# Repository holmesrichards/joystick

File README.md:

# Analog Output Joystick

This is a Kosmo format synth module that provides an interface for an analog joystick. The X and Y outputs provide control voltages that vary with the horizontal and vertical positions, respectively, of the joystick.

There are range control pots for X and Y. These adjust the width of the control voltage range. With the width fully clockwise the control voltage range is about 10 V end to end.

There also are offset control pots. These add a DC offset of between -5 V and 5 V to the output. So with the range pot at maximum and the offset pot centered the output voltage ranges from about -5 V to 5 V; with the offset pot fully clockwise the output voltage range is about 0 V to 10 V.

The X output voltage increases as you move the joystick from left to right, and Y increases from down to up. There also are two inverted output jacks; here the X output increases from right to left and the Y increases from up to down. Both outputs have the same range and same offset (with same sign), so for instance if the regular output is from 0 V to 10 V left to right, the inverted output will be 10 V to 0 V left to right.

## Current draw
16 mA +12 V, 16 mA -12 V

## Photos

## Documentation

* [Schematic](Docs/joystick.pdf)
* PCB layout: [front](Docs/joystick_layout_front.pdf), [back](Docs/joystick_layout_back.pdf)
* [BOM](Docs/joystick_bom.md)
* [Build notes](Docs/build.md)
* [How it works](Docs/howitworks.md)

## GitHub repository

* [https://github.com/holmesrichards/joystick](https://github.com/holmesrichards/joystick)

## Submodules

This repo uses submodules aoKicad and Kosmo_panel, which provide needed libaries for KiCad. To clone:

```
git clone git@github.com:holmesrichards/joystick.git
git submodule init
git submodule update
```

Alternatively do

```
git clone --recurse-submodules git@github.com:holmesrichards/joystick.git
```

Or if you download the repository as a zip file, you must also click on the "aoKicad" and "Kosmo\_panel" links on the GitHub page (they'll have "@ something" after them) and download them as separate zip files which you can unzip into this repo's aoKicad and Kosmo\_panel directories.

If desired, copy the files from aoKicad and Kosmo\_panel to wherever you prefer (your KiCad user library directory, for instance, if you have one). Then in KiCad, add symbol libraries 

```
aoKicad/ao_symbols
Kosmo_panel/Kosmo
```
and footprint libraries 
```
aoKicad/ao_tht
Kosmo_panel/Kosmo_panel.
```

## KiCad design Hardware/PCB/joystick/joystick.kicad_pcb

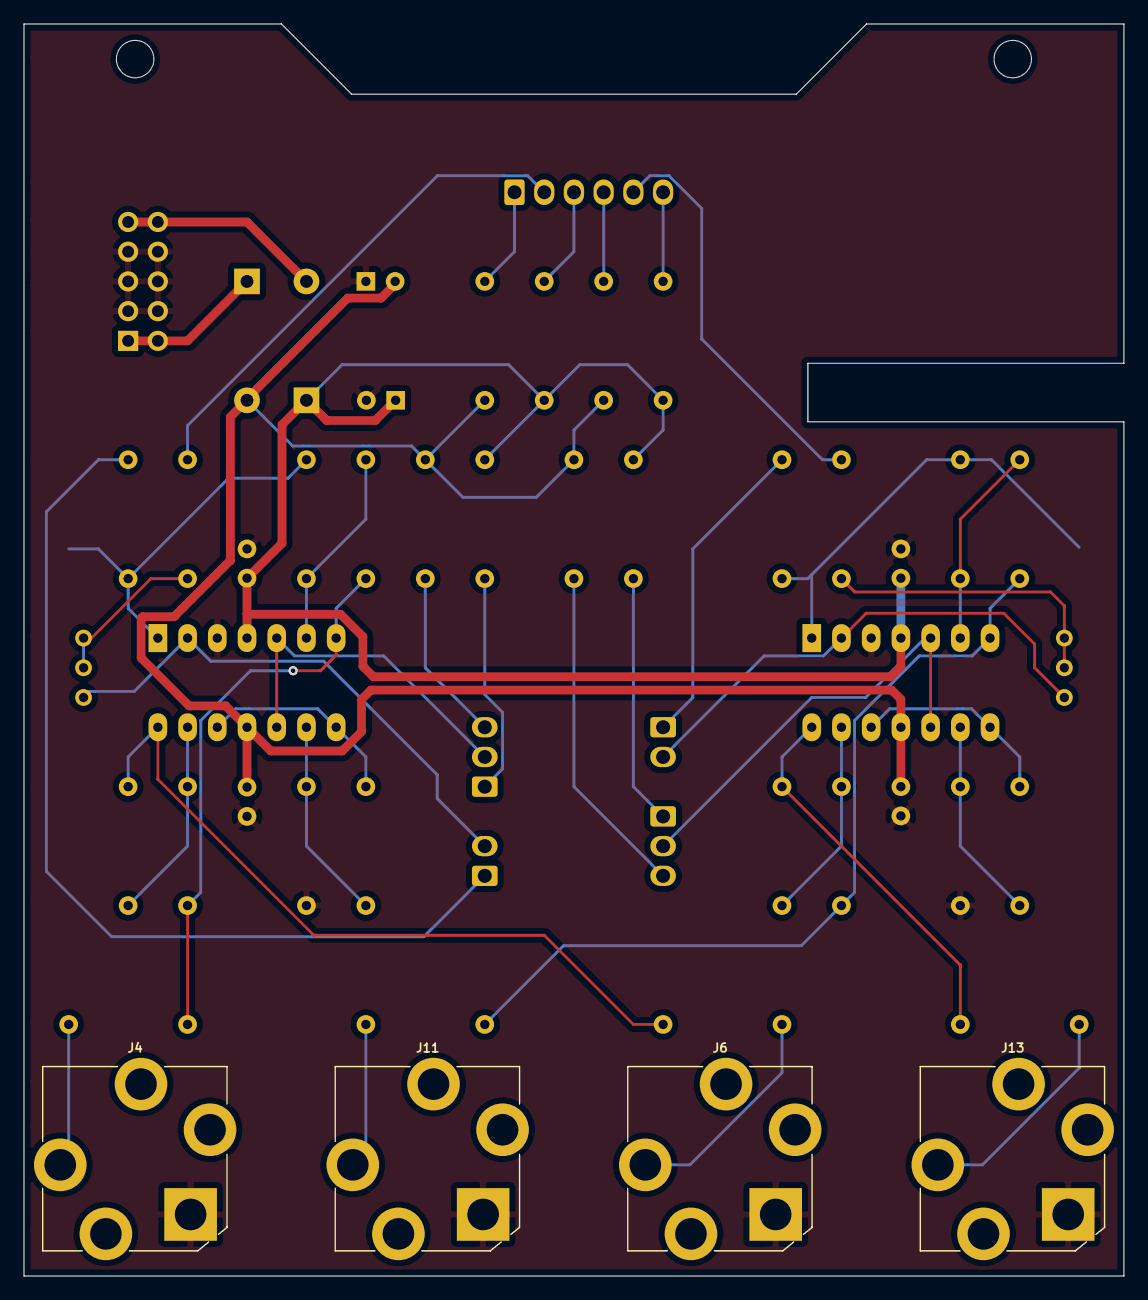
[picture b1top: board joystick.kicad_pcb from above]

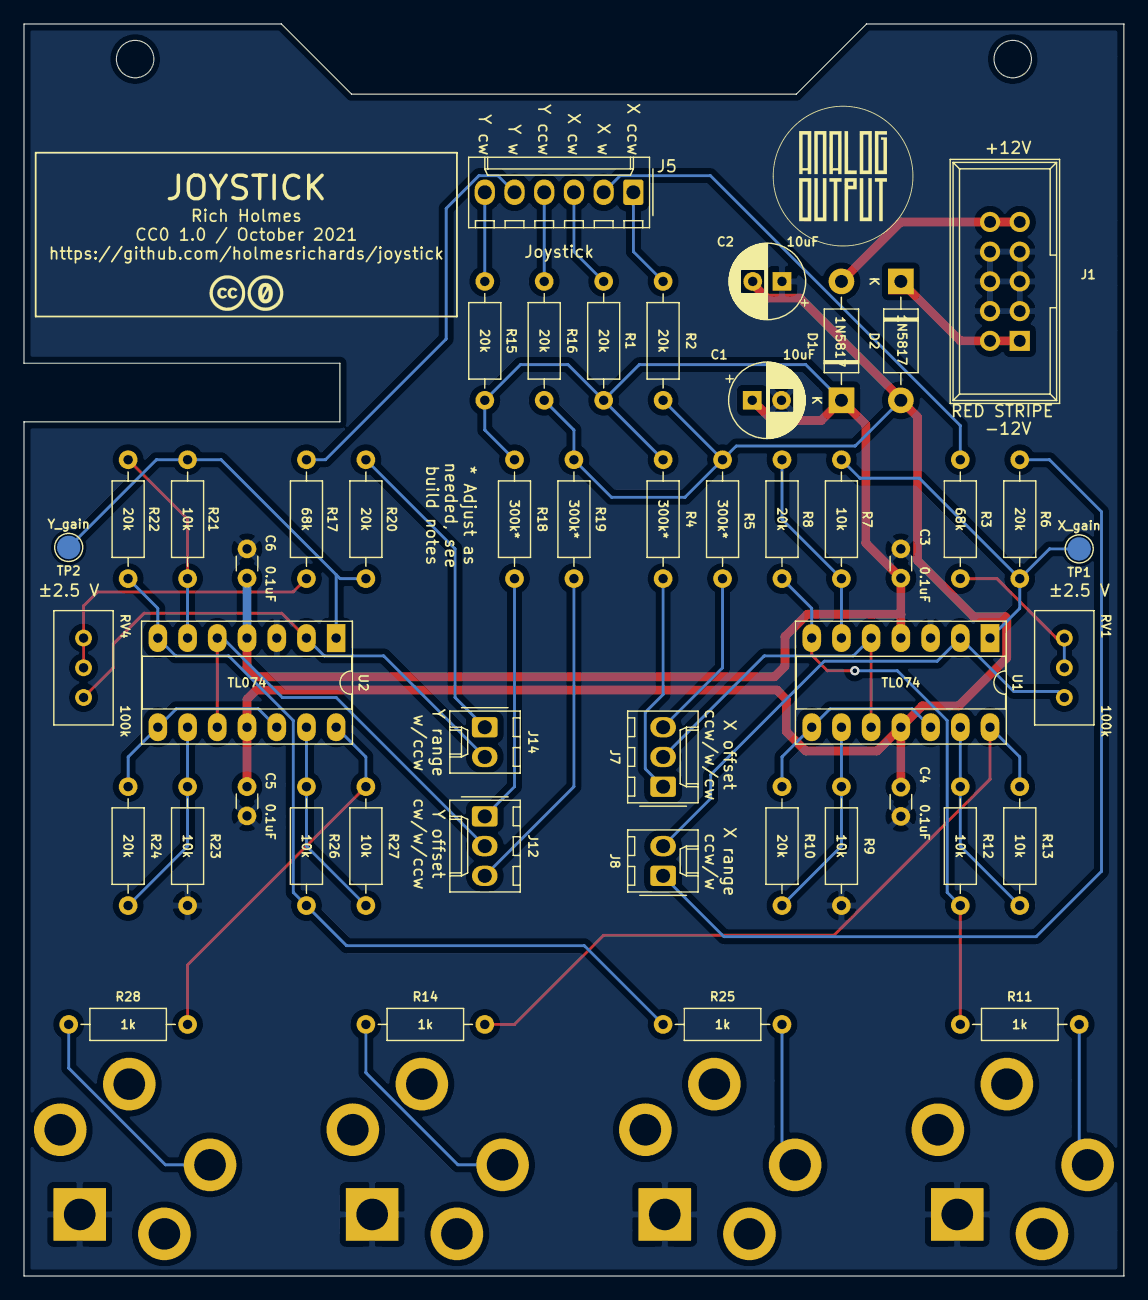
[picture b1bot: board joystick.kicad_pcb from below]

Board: 2 copper layers, 94.0 x 107.0 mm, 57 parts (50 on the bottom side), 41 nets.

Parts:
C1, C2: 10uF; CP_Radial_D6.3mm_P2.50mm
C3, C4, C5, C6: 0.1uF; C_Disc_D3.0mm_W1.6mm_P2.50mm
D1, D2: 1N5817; D_DO-41_SOD81_P10.16mm_Horizontal
GRAF1: Holes; joystick_panel_holes
GRAF2: AO logo; analogoutput_12mm
GRAF3: CC0 logo; CC0_logo
H1, H2: MountingHole; MountingHole_3.2mm_M3
J1: Synth_power_2x5; Power_Header
J4, J6, J11, J13: AudioJack2; Jack_6.35mm_PJ_629HAN
J5: 6 pin Molex header; Molex_KK-254_AE-6410-06A_1x06_P2.54mm_Vertical
J7, J12: 3_pin_Molex_header; Molex_KK-254_AE-6410-03A_1x03_P2.54mm_Vertical
J8, J14: 2_pin_Molex_header; Molex_KK-254_AE-6410-02A_1x02_P2.54mm_Vertical
R1, R2, R6, R8, R10, R15, R16, R20, R22, R24: 20k; R_Axial_DIN0207_L6.3mm_D2.5mm_P10.16mm_Horizontal
R3, R17: 68k; R_Axial_DIN0207_L6.3mm_D2.5mm_P10.16mm_Horizontal
R4, R5, R18, R19: 300k*; R_Axial_DIN0207_L6.3mm_D2.5mm_P10.16mm_Horizontal
R7, R9, R12, R13, R21, R23, R26, R27: 10k; R_Axial_DIN0207_L6.3mm_D2.5mm_P10.16mm_Horizontal
R11, R14, R25, R28: 1k; R_Axial_DIN0207_L6.3mm_D2.5mm_P10.16mm_Horizontal
RV1, RV4: 100k; Potentiometer_Bourns_3296W_Vertical_standard
TP1: X_gain; TestPoint_Pad_D2.0mm
TP2: Y_gain; TestPoint_Pad_D2.0mm
U1, U2: TL074; DIP-14_W7.62mm_Socket_LongPads

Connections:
+12V: C1.1, C3.1, C6.2, D1.1, R1.1, R4.1, R15.1, R18.1, U1.4, U2.4
-12V: C2.2, C4.2, C5.1, D2.2, R2.2, R5.2, R16.2, R19.2, U1.11, U2.11
/+12_IN: D1.2, J1.9, J1.10
/-12_IN: D2.1, J1.1, J1.2
/XOUT: J4.T, R11.1
/Y channel/YOUT: J11.T, R25.1
/Y channel/~YOUT: J13.T, R28.1
/~XOUT: J6.T, R14.1
GND: C1.2, C2.1, C3.2, C4.1, C5.2, C6.1, J1.3, J1.4, J1.5, J1.6, J1.7, J1.8, J4.S, J6.S, J11.S, J13.S, R9.2, R23.2, U1.3, U2.3
unnamed: R3.1, RV1.2, RV1.3
unnamed: R6.1, R7.2, TP1.1, U1.1
unnamed: R7.1, R8.2, U1.6
unnamed: R10.1, U1.8, U1.12
unnamed: R9.1, R10.2, U1.9
unnamed: R8.1, R11.2, R12.2, U1.7
unnamed: R12.1, R13.2, U1.13
unnamed: R13.1, R14.2, U1.14
unnamed: R17.1, RV4.2, RV4.3
unnamed: R20.1, R21.2, TP2.1, U2.1
unnamed: R21.1, R22.2, U2.6
unnamed: R22.1, R25.2, R26.2, U2.7
unnamed: R23.1, R24.2, U2.9
unnamed: R24.1, U2.8, U2.12
unnamed: R26.1, R27.2, U2.13
unnamed: R27.1, R28.2, U2.14
XOFFPOT_CCW: J7.3, R5.1
XOFFPOT_CW: J7.1, R4.2
XOFFPOT_WIPER: J7.2, U1.5, U1.10
XPOT_CCW: J5.1, R2.1
XPOT_CW: J5.3, R1.2
XPOT_WIPER: J5.2, R3.2
XRANGEPOT_CCW: J8.2, RV1.1, U1.2
XRANGEPOT_WIPER: J8.1, R6.2
YOFFPOT_CCW: J12.3, R19.1
YOFFPOT_CW: J12.1, R18.2
YOFFPOT_WIPER: J12.2, U2.5, U2.10
YPOT_CCW: J5.4, R16.1
YPOT_CW: J5.6, R15.2
YPOT_WIPER: J5.5, R17.2
YRANGEPOT_CCW: J14.2, RV4.1, U2.2
YRANGEPOT_WIPER: J14.1, R20.2

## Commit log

2021-10-01 Initial version
2021-10-02 Panel design and Gerbers
2021-10-02 Library updates
2021-10-02 Panel design
2021-10-19 svg internals
2021-10-27 Belated .gitignore; switch to panel mounted pots implying board and panel changes
2021-10-27 Page setup
2021-11-03 Add gain trimmers and test points
2021-11-03 Move trimmers to inputs
2021-11-03 More tweaks, build.md
2021-11-03 Change voltage ranges
2021-11-03 Move trimmers and TPs to back
2021-11-13 Update docs, generate Gerbers
2021-11-29 Correct resistor value
2021-11-30 Fix wrong R value; update documentation; images
2021-11-30 Update libraries
2021-11-30 Create LICENSE
2021-12-01 Correct copy-paste error
2021-12-01 Corrected Gerbers (silkscreen)
2021-12-04 Panel art; revert aoKicad to earlier version
2021-12-04 Don't ignore cache.lib files
2021-12-24 Current draw
2021-12-25 README
2022-03-06 copy and paste typo
2022-06-22 KiCad 6
2022-07-08 Gerbers
